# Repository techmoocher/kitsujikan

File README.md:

# Kitsujikan

A rechargeable, pocket-sized **Pomodoro timer** with an OLED display and colour-coded buttons, designed for [Hack Club](https://hackclub.com)'s **Half-Life** 10-week hardware challenge.

| Front                                         | Back                                        |
|-----------------------------------------------|---------------------------------------------|
|  |  |

## Features

- **One-press focus sessions:** 30, 60 or 90 minutes, one button each.
- **Automatic breaks:** when a session ends, the buzzer sounds and the timer offers a 5-minute break. Press **green** to accept or **red** to skip. After the break, it offers to repeat the last session length.
- **Clear display:** a 0.96" OLED shows the time left as `HH:MM:SS`. Hours are hidden when zero, and minutes and seconds always show two digits.
- **Pause:** press **red** during a session.
- **Battery powered:** runs from a LiPo battery and charges over USB-C, with an on/off switch and battery-level sensing.
- **Low power:** sleeps when idle, and the 30/60/90 buttons wake it from deep sleep.

## Status

- [x] Schematic
- [x] PCB layout and routing (DRC clean)
- [x] Gerber and drill files
- [x] Bill of materials (BOM)
- [ ] Order the PCB and parts
- [x] Firmware: first version (untested on hardware)
- [ ] Assembly and testing
- [ ] Enclosure

## Hardware

| Power | 3.7 V LiPo (JST-PH), slide switch, 2 × 200 kΩ battery-sense divider |
| PCB   | 2 layers, 65 × 90 mm, all through-hole parts                        |

### Pin map

| XIAO pin  | GPIO  | Connected to                        | Why this pin                                                                          |
|-----------|-------|-------------------------------------|---------------------------------------------------------------------------------------|
| D0        | 2     | 30-min button (+10 kΩ pull-up)      | Can wake from deep sleep; it's a strapping pin, so the pull-up holds it high at boot  |
| D1        | 3     | 60-min button                       | Can wake from deep sleep                                                              |
| D2 / A2   | 4     | Battery voltage (divider midpoint)  | Calibrated ADC1 channel                                                               |
| D3        | 5     | 90-min button                       | Can wake from deep sleep; its ADC2 channel is unreliable anyway                       |
| D4 / D5   | 6 / 7 | I2C SDA / SCL (OLED)                | Default I2C pins                                                                      |
| D6        | 21    | Red No/Pause button                 | Not a strapping pin                                                                   |
| D7        | 20    | Buzzer transistor                   | Input at boot, so the buzzer stays quiet                                              |
| D10       | 10    | Green OK button                     | General purpose                                                                       |
| D8, D9    | 8, 9  | Unused                              | Strapping pins (D9 is the BOOT button)                                                |

## Directory structure

```plaintext
PCB/                 KiCad 10 project (schematic + board)
PCB/libs/            Symbol, footprint and 3D libraries used by the project
PCB/production/      Gerber and drill files for manufacturing
renders/             3D renders of the board
Firmware/            Arduino firmware for the XIAO ESP32-C3
kitsujikan_BOM.csv   Bill of materials with sources and estimated prices
```

## Bill of materials

The full list with links is in [`kitsujikan_BOM.csv`](kitsujikan_BOM.csv). Summary:

| Qty | Part                                                      | Source          |
|-----|-----------------------------------------------------------|-----------------|
| 1   | Seeed Studio XIAO ESP32-C3                                | Seeed Studio    |
| 1   | 0.96" SSD1306 I2C OLED (pins: GND, VCC, SCL, SDA)         | Amazon          |
| 5   | 12×12 mm tactile switches with coloured caps              | Amazon          |
| 1   | C&K OS102011MS2QN1 slide switch                           | LCSC / DigiKey  |
| 1   | JST-PH 2-pin side-entry socket (S2B-PH-K-S)               | LCSC / DigiKey  |
| 1   | 3.7 V ~500 mAh LiPo with protection circuit, JST-PH plug  | Amazon          |
| 1   | Passive buzzer, 12 mm                                     | Amazon          |
| 1   | 2N3904 transistor, 1N4148 diode                           | Amazon          |
| 5   | Resistors: 2 × 200 kΩ, 2 × 10 kΩ, 1 × 1 kΩ                | Amazon          |
| 1   | 100 nF ceramic capacitor                                  | Amazon          |
| —   | Female pin headers (1×7 ×2, 1×4 ×1), thin wire            | Amazon          |
| 5   | PCBs                                                      | JLCPCB          |

Prices in the CSV are rough estimates. Many Amazon items come in multi-packs, so the first build costs more than the parts on one board.

## Ordering the PCB

1. Zip the contents of `PCB/production/`.
2. Upload the zip at [jlcpcb.com](https://jlcpcb.com).
3. The defaults work: 2 layers, 1.6 mm, HASL. Pick any solder mask colour.

## Notes on assembly

- **Mount the XIAO on female headers, not flat.** The battery connects to pads on its *underside* (BAT+ / BAT−). Solder two short wires to those pads, thread them through the **J2** holes, and solder them on the back.
- **Check the OLED pin order** before soldering its socket. This board expects **GND, VCC, SCL, SDA**.
- **Check the LiPo plug polarity** before plugging it in. **J1 pin 1 is +.** Battery plug colours aren't standardised.
- **Charging only works with the power switch ON**, because the switch disconnects the battery.
- **Keep the battery away from the sharp solder joints on the back.** Use foam tape, or standoffs and a back plate.
- Solder the low parts first (resistors, diode), then the transistor, buzzer, switches and headers.

## Firmware

Arduino (C++) for the ESP32-C3, in [`Firmware/`](Firmware/). It covers the timer state machine, debounced buttons (tap / hold), buzzer melodies, the OLED screens, battery percentage, and deep sleep with wake-on-button. Build steps and controls are in [`Firmware/README.md`](Firmware/README.md). The timer logic has laptop unit tests in `Firmware/test/`.

## Acknowledgements

- [Hack Club](https://hackclub.com) and the Half-Life challenge
- [Starbie](https://github.com/SharKingStudios/Starbie), the Half-Life Week 1 example project, and its care-package libraries
- Seeed Studio for the XIAO KiCad symbol library

## License

This project is released under the [MIT License](LICENSE). Third-party libraries in `PCB/libs/` remain under their original authors' licenses.

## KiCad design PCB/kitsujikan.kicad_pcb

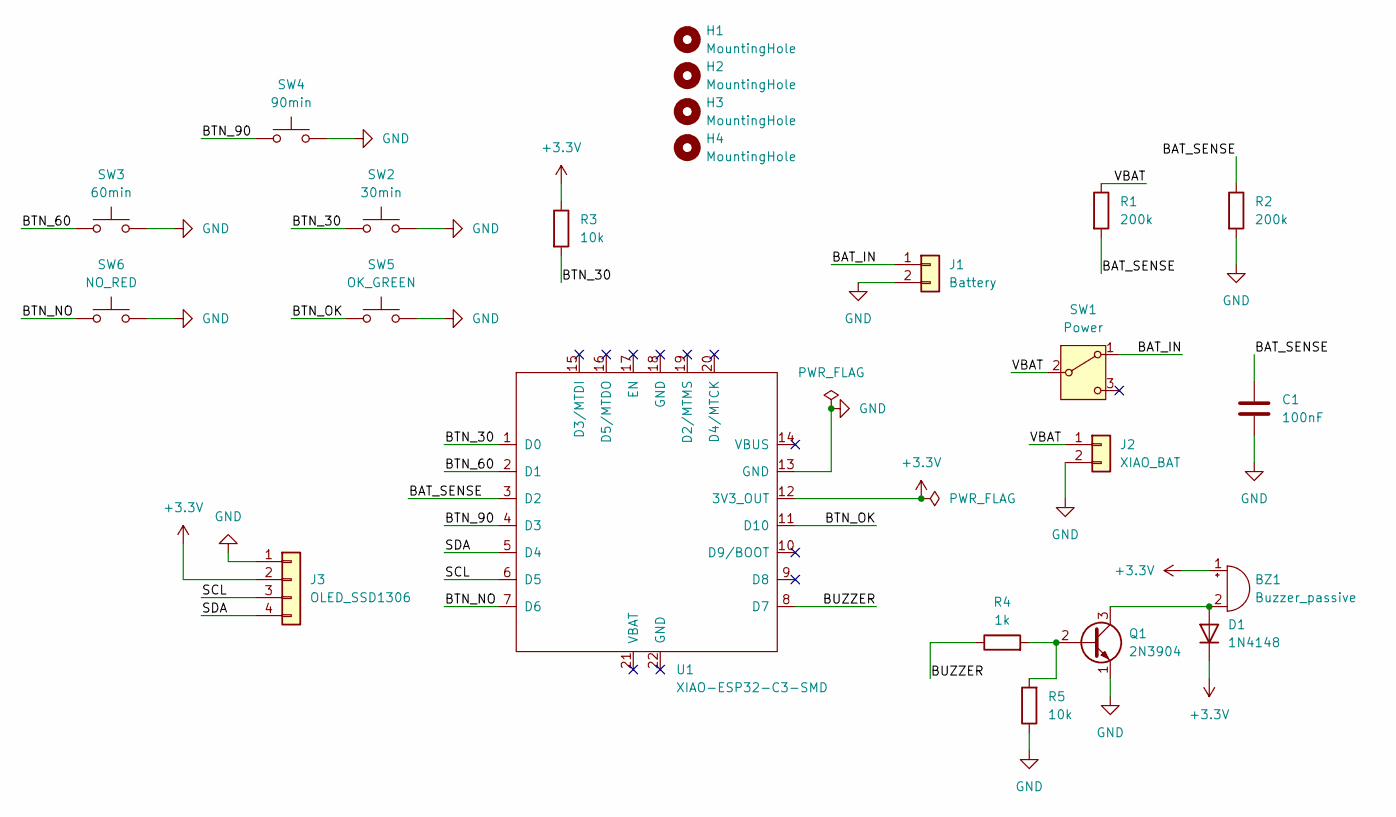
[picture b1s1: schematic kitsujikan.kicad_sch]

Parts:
BZ1: Buzzer_passive; Buzzer_12x9.5RM7.6
C1: 100nF; C_Disc_D5.0mm_W2.5mm_P5.00mm
D1: 1N4148; D_DO-35_SOD27_P7.62mm_Horizontal
H1, H2, H3, H4: MountingHole; MountingHole_3.2mm_M3
J1: Battery; JST_PH_S2B-PH-K_1x02_P2.00mm_Horizontal
J2: XIAO_BAT; SolderWire-0.15sqmm_1x02_P4mm_D0.5mm_OD1.5mm
J3: OLED_SSD1306; Display_128x64_096_I2C
Q1: 2N3904; TO-92_Inline
R1, R2: 200k; R_Axial_DIN0207_L6.3mm_D2.5mm_P10.16mm_Horizontal
R3, R5: 10k; R_Axial_DIN0207_L6.3mm_D2.5mm_P10.16mm_Horizontal
R4: 1k; R_Axial_DIN0207_L6.3mm_D2.5mm_P10.16mm_Horizontal
SW1: Power; SW_Slide_SPDT_Straight_CK_OS102011MS2Q
SW2: 30min; SW_PUSH-12mm
SW3: 60min; SW_PUSH-12mm
SW4: 90min; SW_PUSH-12mm
SW5: OK_GREEN; SW_PUSH-12mm
SW6: NO_RED; SW_PUSH-12mm
U1: XIAO-ESP32-C3-SMD; XIAO-ESP32-C6-DIP

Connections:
+3.3V: BZ1.1 (+), D1.1 (K), J3.2, R3.1, U1.12 (3V3_OUT)
/BAT_IN: J1.1, SW1.1 (A)
/BAT_SENSE: C1.1, R1.2, R2.1, U1.3 (D2)
/BTN_30: R3.2, SW2.1, U1.1 (D0)
/BTN_60: SW3.1, U1.2 (D1)
/BTN_90: SW4.1, U1.4 (D3)
/BTN_NO: SW6.1, U1.7 (D6)
/BTN_OK: SW5.1, U1.11 (D10)
/BUZZER: R4.1, U1.8 (D7)
/SCL: J3.3, U1.6 (D5)
/SDA: J3.4, U1.5 (D4)
/VBAT: J2.1, R1.1, SW1.2 (B)
GND: C1.2, J1.2, J2.2, J3.1, Q1.1 (E), R2.2, R5.1, SW2.2, SW3.2, SW4.2, SW5.2, SW6.2, U1.13 (GND)
unnamed: BZ1.2 (-), D1.2 (A), Q1.3 (C)
unnamed: Q1.2 (B), R4.2, R5.2

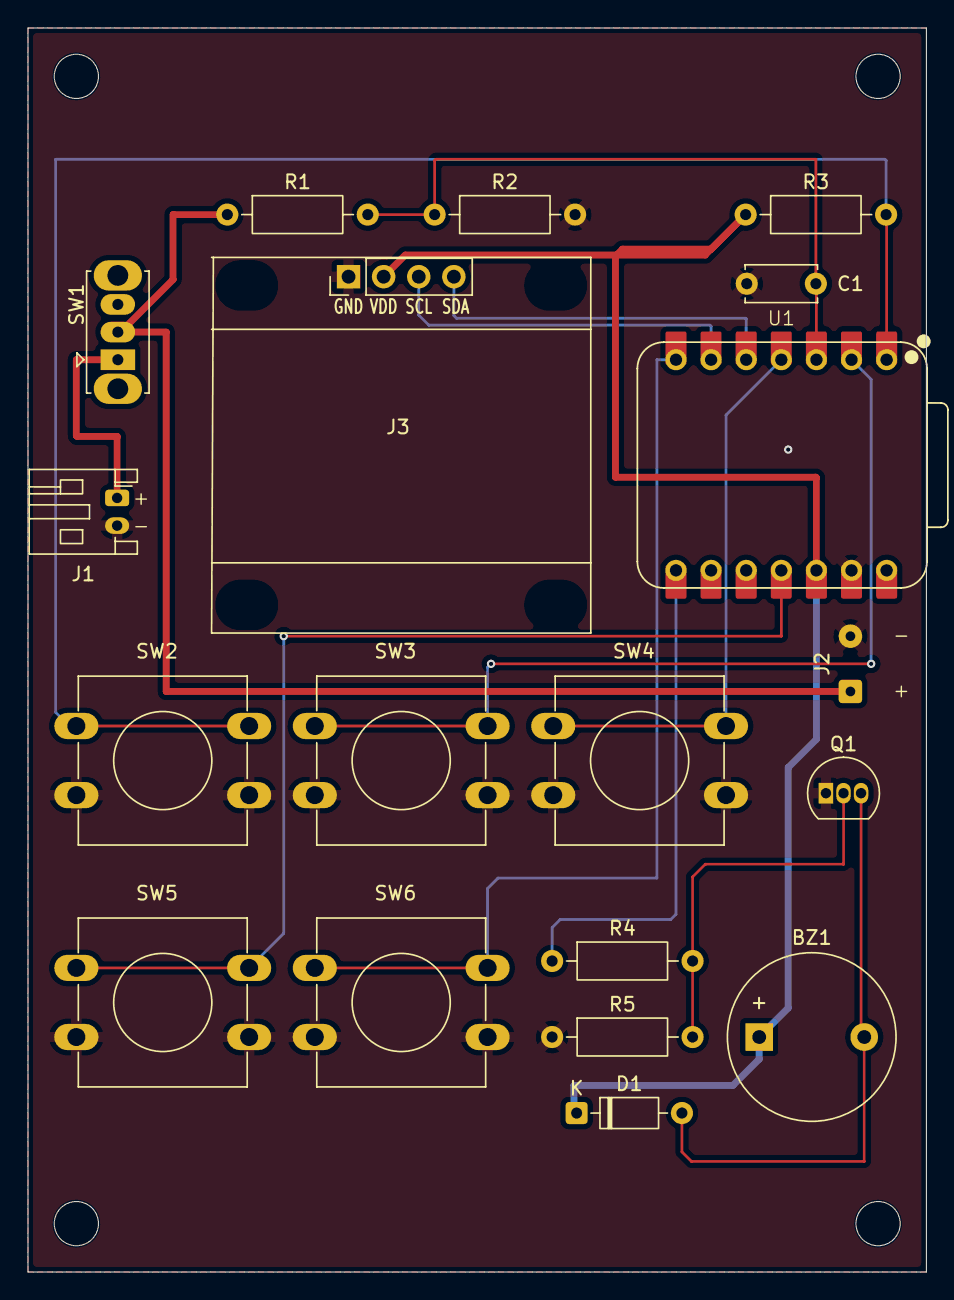
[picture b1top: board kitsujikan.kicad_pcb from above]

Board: 2 copper layers, 65.0 x 90.0 mm, 23 parts (0 on the bottom side), 15 nets.

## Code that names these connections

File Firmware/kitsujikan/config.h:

// config.h: every pin number and timing value lives here.
// Pin numbers are ESP32-C3 GPIO numbers; the XIAO silkscreen label is in the comment.
// They match the schematic (see README "Pin map").
#pragma once
#include <stdint.h>

// ---------------- Pins ----------------
constexpr uint8_t PIN_BTN_30 = 2;   // D0  30-min button (strapping pin, 10k external pull-up)
constexpr uint8_t PIN_BTN_60 = 3;   // D1  60-min button
constexpr uint8_t PIN_BAT    = 4;   // D2  battery voltage, through a 1:2 divider (200k + 200k)
constexpr uint8_t PIN_BTN_90 = 5;   // D3  90-min button
constexpr uint8_t PIN_SDA    = 6;   // D4  OLED SDA
constexpr uint8_t PIN_SCL    = 7;   // D5  OLED SCL
constexpr uint8_t PIN_BTN_NO = 21;  // D6  red button: no / pause (hold = stop)
constexpr uint8_t PIN_BUZZER = 20;  // D7  buzzer transistor base (via 1k)
constexpr uint8_t PIN_BTN_OK = 10;  // D10 green button: ok / continue

constexpr uint8_t OLED_ADDR = 0x3C;  // most 0.96" SSD1306 modules

// ---------------- Timing ----------------
// While testing, set FAST_TEST to 1: every "minute" then lasts 1 second,
// so a 30-min session takes 30 s and the 5-min break takes 5 s.
#define FAST_TEST 0

#if FAST_TEST
constexpr uint32_t MINUTE_MS = 1000UL;
#else
constexpr uint32_t MINUTE_MS = 60UL * 1000UL;
#endif

constexpr uint32_t BREAK_MINUTES     = 5;
constexpr uint32_t PROMPT_TIMEOUT_MS = 5UL * 60UL * 1000UL;  // stop asking after 5 min with no answer
constexpr uint32_t IDLE_SLEEP_MS     = 60UL * 1000UL;        // deep sleep after 1 min idle
constexpr uint32_t DEBOUNCE_MS       = 25;                   // ignore contact bounce shorter than this
constexpr uint32_t LONG_PRESS_MS     = 800;                  // hold red this long = stop
constexpr uint32_t REDRAW_MS         = 250;                  // screen refresh period
constexpr uint32_t BATTERY_SAMPLE_MS = 5000;                 // battery reading period
